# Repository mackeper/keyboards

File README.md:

# Keyboards

<div align="center">

Collection of my keyboards and keymaps.

[Keyboards](#keyboards-keyboard) •
[Dependencies](#dependencies-package) •
[Related Projects](#related-projects-link)

</div>

## Keyboards :keyboard:

#### Fat cruiser

* [v1](./fat_cruiser/v1/README.md)
  <details>
  <summary>Preview</summary>

  </details>
* [v2](./fat_cruiser/v2/README.md)
  <details>
  <summary>Preview</summary>

  </details>

## Dependencies :package:

* [KiCad](https://www.kicad.org/)
* [Ergogen](https://github.com/ergogen/ergogen)
  * Install with `npm install -g ergogen`
* [QMK](https://qmk.fm/)
  * Clone or fork the [QMK repository](https://github.com/qmk/qmk.fm)
  * Optional: [Bear](https://github.com/rizsotto/Bear)
    * sudo apt-get install bear
    * bear -- make <keyboard>:<keymap>

## Miscellanceous :sparkles:

### Vim magic

Useful find and replace to add a value to all the coordinates in a KiCad file.

```Vim
:'<,'>s/-*\d\+\.\d\+/\=str2float(submatch(0))+13.97/`
```

### KiCad tips

* Set rotation step to match your keyboard for easier rotation of components
  * See below
* Tools -> Clean up tracks and vias
* Edit -> Edit teardrops
  * Add teardrops to pads for stronger connections to tracks
* Route -> Design Rules Checker
  * Check for errors in your PCB design

#### KiCad Preferences

Set the rotation step to the same value as your keyboard's rotation.

## Related Projects :link:

* <https://github.com/benvallack/ergogen>

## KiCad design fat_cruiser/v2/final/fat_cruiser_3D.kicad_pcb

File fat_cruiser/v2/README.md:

# Fat Cruiser v2

<div align="center">

<!--  -->

</div>

See [keymap layout](./qmk/readme.md).

### Images :camera:

<details>
  <summary>Click to expand</summary>
  <div align="center">
    
  </div>
<div align="center">
</details>

### Changes from v1:
  - Design
    - Increate rotation from 10° to 12°
    - A bit less staggered
      - v1: 0, 16, 7, -5, -5
      - v2: 0, 12, 7, -5, -2
    - Add angle and splay to thumb cluster
      - The thumb should now rest at the center key
  - Hardware
    - Switch to nice!nano v2 (from Raspberry Pi Pico H)
      - Add sockets for MCU
    - Move the diodes to front, inbetween the switches
    - Change switches to Kalih choc redpro (from Kalih choc purple)
      - Hot swappable
    - Change keycaps to MoErgo POM MCC-Profile 1U Keycap (from blank MBK Choc U1)

### Dependencies :gear:

- [KiCad](https://www.kicad.org/)
- [QMK](https://qmk.fm/)
- [Ergogen](https://github.com/berigora/ergogen)
    - `npm install -g ergogen`
- [jscad](https://github.com/jscad/OpenJSCAD.org)
    - `npm install -g @jscad/cli` (this does not work with ergogen generated jscad files yet)
    - `npm install -g @jscad/openjscad` (old version, but works with ergogen generated jscad files)

### Build :hammer:

From within `fat_cruiser/v2/`:

- `ergogen . && for i in output/cases/*.jscad; do npx @jscad/cli@1 "$i" -of stla; done`

### KiCad plot pcb :printer:

- Open pcb in KiCad
- File -> Page Settings
    - Set to A4
- File -> Plot
  - Plot format: PDF
  - Include layers:
    - F.Cu
  - Plot on all layers:
    - F.Cu
    - B.Cu
    - F.Fab
    - B.Fab
    - F.SilkS
    - F.Mask
    - B.Mask
    - Edge.Cuts
    - User.Drawings
    - User.Comments
    - F.Courtyard
    - B.Courtyard
  - Plot drawing sheet
  - Drill marks
    - Actual size
  - Sketch pads on fabrication layers
  - Select output directory

### Parts :nut_and_bolt:

| Part                                          | Price                       | Url                                                                                                                     |
| ----------------                              | ---------------             | ---------------                                                                                                         |
| PCB                                           | €12.94 (+ €17.39 shipping)  | [jlcpcb](https://jlcpcb.com/)                                                                                           |
| 40 Switches (Kalih choc redpro)               | €23.96                      | [splitkb](https://splitkb.com/products/kailh-low-profile-choc-switches?variant=33100108234829)                          |
| 40 Keycaps (MoErgo POM MCC-Profile 1U Keycap) | €19.96                      | [splitkb](https://splitkb.com/products/moergo-mcc-profile-1u-keycap?_pos=3&_sid=99ef29720&_ss=r&variant=42898211602691) |
| 100 SMD Diodes                                | €2.49                       | [splitkb](https://splitkb.com/products/kailh-hotswap-sockets?_pos=1&_sid=9303a7619&_ss=r)                               |
| nice!nano v2                                  | €25.94                      | [splitkb](https://splitkb.com/products/nice-nano?_pos=1&_sid=33e2bd019&_ss=r)                                           |
| SSD1306 OLED Display                          | €5.89                       | [splitkb](https://splitkb.com/products/oled-display?_pos=1&_sid=de7400663&_ss=r&variant=31226608549965)                 |
| Kailh Hotswap Sockets                         | €7.95                       | [splitkb](https://splitkb.com/products/kailh-hotswap-sockets?_pos=1&_sid=9303a7619&_ss=r)                               |
| Battery 110 mah                               |                             |                                                                                                                         |
| Connector                                     |                             |                                                                                                                         |
| Power switch                                  |                             |                                                                                                                         |
| Mill Max Low Profile Sockets                  | €11.45                      | [splitkb](https://splitkb.com/products/mill-max-low-profile-sockets?variant=47060695646555)                             |
| Total                                         | €55.12                      |                                                                                                                         |

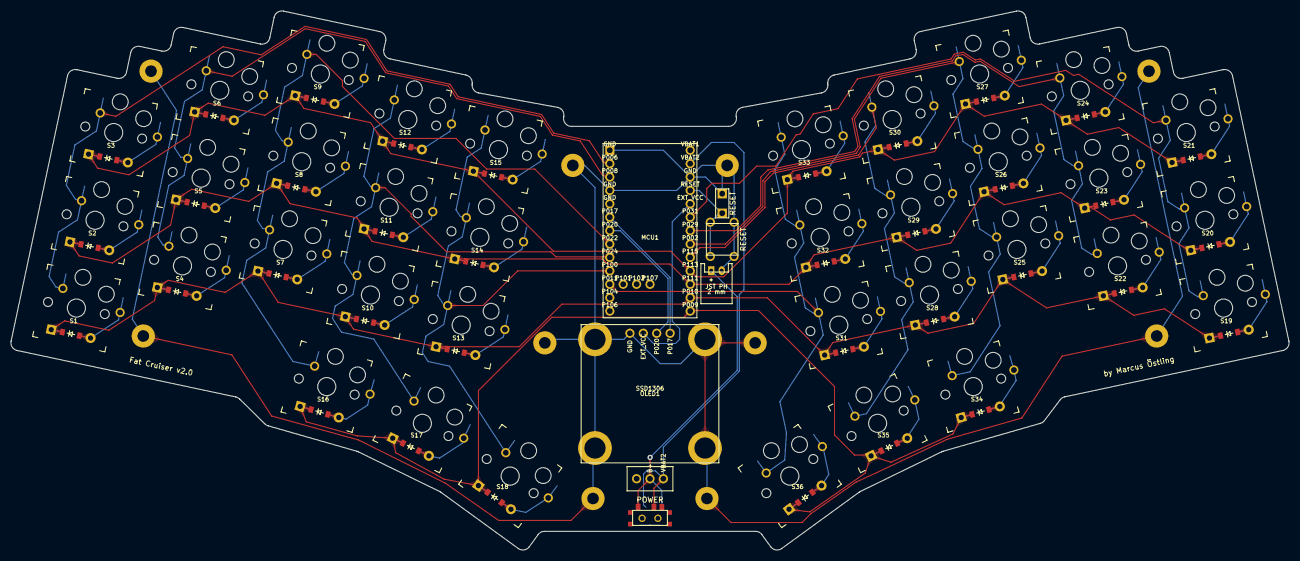
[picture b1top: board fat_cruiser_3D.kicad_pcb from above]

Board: 2 copper layers, 242.2 x 102.1 mm, 93 parts (0 on the bottom side), 57 nets.

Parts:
B1: Button2pin
B2: Button4pin
D1, D2, D3, D4, D5, D6, D7, D8, D9, D10, D11, D12, D13, D14, D15, D16, D17, D18, D19, D20, D21, D22, D23, D24, D25, D26, D27, D28, D29, D30, D31, D32, D33, D34, D35, D36: ComboDiode
JST1: JST_PH_S2B-PH-K_02x2.00mm_Angled
MCU1: NiceNano
MH1, MH2, MH3, MH4, MH5, MH6, MH7, MH8, MH9, MH10: MountingHole_Pad_Via
OLED1: OLED_SSD1306
S1, S2, S3, S4, S5, S6, S7, S8, S9, S10, S11, S12, S13, S14, S15, S16, S17, S18, S19, S20, S21, S22, S23, S24, S25, S26, S27, S28, S29, S30, S31, S32, S33, S34, S35, S36: PG1350
T1, T2, T3: text
T4, T5: SPDT_C128955
T6: Slider3Pin

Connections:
B+: JST1.1, T4.1, T5.1, T6.1
EXT_VCC: MCU1.4, OLED1.7
GND: B1.2, B2.3, B2.4, JST1.2, MCU1.0, MCU1.2, MCU1.3, MCU1.4, OLED1.1, OLED1.2, OLED1.3, OLED1.4, OLED1.8
P002: MCU1.7, S25.1, S26.1, S27.1, S34.1
P006: MCU1.1, S1.1, S2.1, S3.1
P008: MCU1.2, S4.1, S5.1, S6.1
P009: D16.1, D17.1, D18.1, D34.1, D35.1, D36.1, MCU1.12
P010: D1.1, D4.1, D7.1, D10.1, D13.1, D19.1, D22.1, D25.1, D28.1, D31.1, MCU1.11
P011: MCU1.10, S31.1, S32.1, S33.1, S36.1
P017: MCU1.5, OLED1.5
P020: MCU1.6, OLED1.6
P022: MCU1.7, S7.1, S8.1, S9.1, S16.1
P024: MCU1.8, S10.1, S11.1, S12.1, S17.1
P029: MCU1.6, S22.1, S23.1, S24.1
P031: MCU1.5, S19.1, S20.1, S21.1
P100: MCU1.9, S13.1, S14.1, S15.1, S18.1
P111: D2.1, D5.1, D8.1, D11.1, D14.1, D20.1, D23.1, D26.1, D29.1, D32.1, MCU1.10
P113: D3.1, D6.1, D9.1, D12.1, D15.1, D21.1, D24.1, D27.1, D30.1, D33.1, MCU1.9
P115: MCU1.8, S28.1, S29.1, S30.1, S35.1
RESET: B1.1, B2.1, B2.2, MCU1.3
VBAT2: MCU1.1, T4.2, T5.2, T6.2
far_bottom: D13.2, S13.2
far_home: D14.2, S14.2
far_thumb: D18.2, S18.2
far_top: D15.2, S15.2
index_bottom: D10.2, S10.2
index_home: D11.2, S11.2
index_thumb: D17.2, S17.2
index_top: D12.2, S12.2
middle_bottom: D7.2, S7.2
middle_home: D8.2, S8.2
middle_thumb: D16.2, S16.2
middle_top: D9.2, S9.2
mirror_far_bottom: D31.2, S31.2
mirror_far_home: D32.2, S32.2
mirror_far_thumb: D36.2, S36.2
mirror_far_top: D33.2, S33.2
mirror_index_bottom: D28.2, S28.2
mirror_index_home: D29.2, S29.2
mirror_index_thumb: D35.2, S35.2
mirror_index_top: D30.2, S30.2
mirror_middle_bottom: D25.2, S25.2
mirror_middle_home: D26.2, S26.2
mirror_middle_thumb: D34.2, S34.2
mirror_middle_top: D27.2, S27.2
mirror_pinky_bottom: D19.2, S19.2
mirror_pinky_home: D20.2, S20.2
mirror_pinky_top: D21.2, S21.2
mirror_ring_bottom: D22.2, S22.2
mirror_ring_home: D23.2, S23.2
mirror_ring_top: D24.2, S24.2
pinky_bottom: D1.2, S1.2
pinky_home: D2.2, S2.2
pinky_top: D3.2, S3.2
ring_bottom: D4.2, S4.2
ring_home: D5.2, S5.2
ring_top: D6.2, S6.2

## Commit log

2024-05-09 Add fat cruiser
2024-05-09 add mounting holes to rp2040
2024-05-09 change gpio for rows and cols
2024-05-09 add pcb file
2024-05-10 Work on pcb
2024-05-10 Add gerber files
2024-05-10 Change image
2024-05-10 Add docs
2024-05-11 Add parts
2024-06-03 Add qmk files
2024-06-05 Add new image
2024-06-05 Add images and minor change to config.h
2024-06-08 work on gaming layer
2024-06-10 Gaming layer and formatting
2024-06-13 Update keymap and add image
2024-06-13 Add link to keymap
2024-06-19 Add some remarks
2024-06-19 Start with v2
2024-06-19 Start working on 3d printable cases
2024-06-25 Add remark
2024-08-09 Update qmk and v2
2024-08-09 add splay
2024-08-18 Fix oled and some cutout points
2024-08-29 Work on v2
2025-01-10 Update keymap for gaming layer
2025-01-10 Update keymap image
2025-10-14 Fix enter and start with auto click feature
2025-10-20 Add fat_cruiser v2 updates
2025-11-30 Working on fat_cruiser v2
2025-11-30 Create case base
2025-11-30 Add plate case
2025-12-01 Add segments connecting SMD pads to THT pads/vias
2025-12-01 Add GitHub Actions workflow for v2
2025-12-01 Move workflow to repository root
2025-12-01 Add neovim to workflow
2025-12-01 Replace nvim with platform-specific sed/PowerShell
2025-12-03 Fix nets
2025-12-13 ordered final
2025-12-16 Added 3D models to the kicad footprints
2025-12-16 Add 3D model progress image
2025-12-21 Update the case
2026-01-10 Added v2-rev1, same features just a few updates to footprints and config
